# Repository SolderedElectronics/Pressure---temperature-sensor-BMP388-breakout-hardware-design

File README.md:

# Pressure & temperature sensor  BMP388 breakout Hardware Design

## About the Product

|  |
| :----------------------------------------------------------: |
| [Buy Pressure & temperature sensor  BMP388 breakout](https://www.solde.red/333316) |

<INSERT PRODUCT DESCRIPTION>

---

## Repository Contents

This repository contains all design files for Pressure & temperature sensor  BMP388 breakout, organized as follows:

- **`CAD` folder**: Contains KiCAD design files, including:
  - Schematics
  - PCB layout
  - Panel PCB layout
  - Source 3D files in Fusion360, if any
  - All files are sorted by version with a detailed change log.
- **`OUTPUTS` folder**: Includes all production-ready files, such as:
  - Bill of Materials (BOM) and interactive BOM (iBOM)
  - PDF versions of schematics
  - 3D `.step` file of the board
  - 3D-printable models
  - Gerber files for PCB manufacturing
  - Image of the pinout of the board
  - Product image
  - Compliance, legal and generic sales documents

Refer to the `Change Log` in the CAD folder for details about updates between versions.

---

## Learn More About the Product

Beyond the repository, explore the following resources:

### Soldered Verify

The **Soldered Verify** system ensures every board you purchase from Soldered is fully functional. It also provides access to exclusive test data for your product. To get started, find the unique Soldered Verify ID on your product's packaging and enter the ID on the [Soldered Verify page](https://soldered.com/verify/) to access test results and additional product details.

### Soldered Community

Soldered Community is your go-to place for technical support. Our engineers track and answer all questions posted there, and it’s a great space for the maker community. Get answers to your questions and solutions for your challenges at [Soldered Community](https://soldered.com/community).

### solde.red

solde.red is an ultimate URL shortener and information hub. Access it by typing solde.red/ followed by your product SKU, e.g., [solde.red/333000](https://solde.red/333000), to find getting-started guides, datasheets, open-source hardware and software files, certifications, images, pinouts, and more. Read more about the shortener [here](https://solde.red/info/).

---

## Contributing

Contributions are welcome! Here’s how you can get involved:

- Submit pull requests to enhance the design or fix issues.
- Report bugs or problems by opening an issue.

We encourage community collaboration to make this product even better.

---

## About Soldered

[Soldered for Makers](https://soldered.com) specializes in designing and manufacturing electronic products tailored for enthusiasts, ranging from hobbyists to professionals. Our portfolio includes electronic boards, sensors, and actuators that are widely utilized in fields such as microelectronics, mechatronics, robotics, programming, and IoT. Every product we offer is designed in-house and built upon open-source hardware and software platforms. Proudly certified and manufactured within the European Union, our catalog likely includes the product you need for your project.

We complement these products with comprehensive tutorials and manuals, product descriptions, schematics, programming codes, and project examples. Our round-the-clock [customer and technical support](https://soldered.com/community) is available for all our products, irrespective of the sales channel. Soldered’s success and services reflect our maker community’s unwavering [trust](https://www.trustpilot.com/review/soldered.com), for which we are deeply grateful. Join our community and create using Soldered products.

---

## License

All Soldered open-source hardware (OSH) is under The TAPR Open Hardware License. Read more in the LICENSE file located in this repository.

**Disclaimer:**

No warranty - all designs in this repository are distributed in the hope that they will be useful, but without any warranty. They are provided "AS IS", therefore without warranty of any kind, either expressed or implied. The entire quality and performance of what you do with the contents of this repository are your responsibility. In no event Soldered Electronics will be liable for your damages, or losses, including any general, special, incidental, or consequential damage arising out of the use or inability to use the contents of this repository. 

---

## Have fun!

Thank you for your support from your fellow makers at Soldered Electronics.

Happy Making!

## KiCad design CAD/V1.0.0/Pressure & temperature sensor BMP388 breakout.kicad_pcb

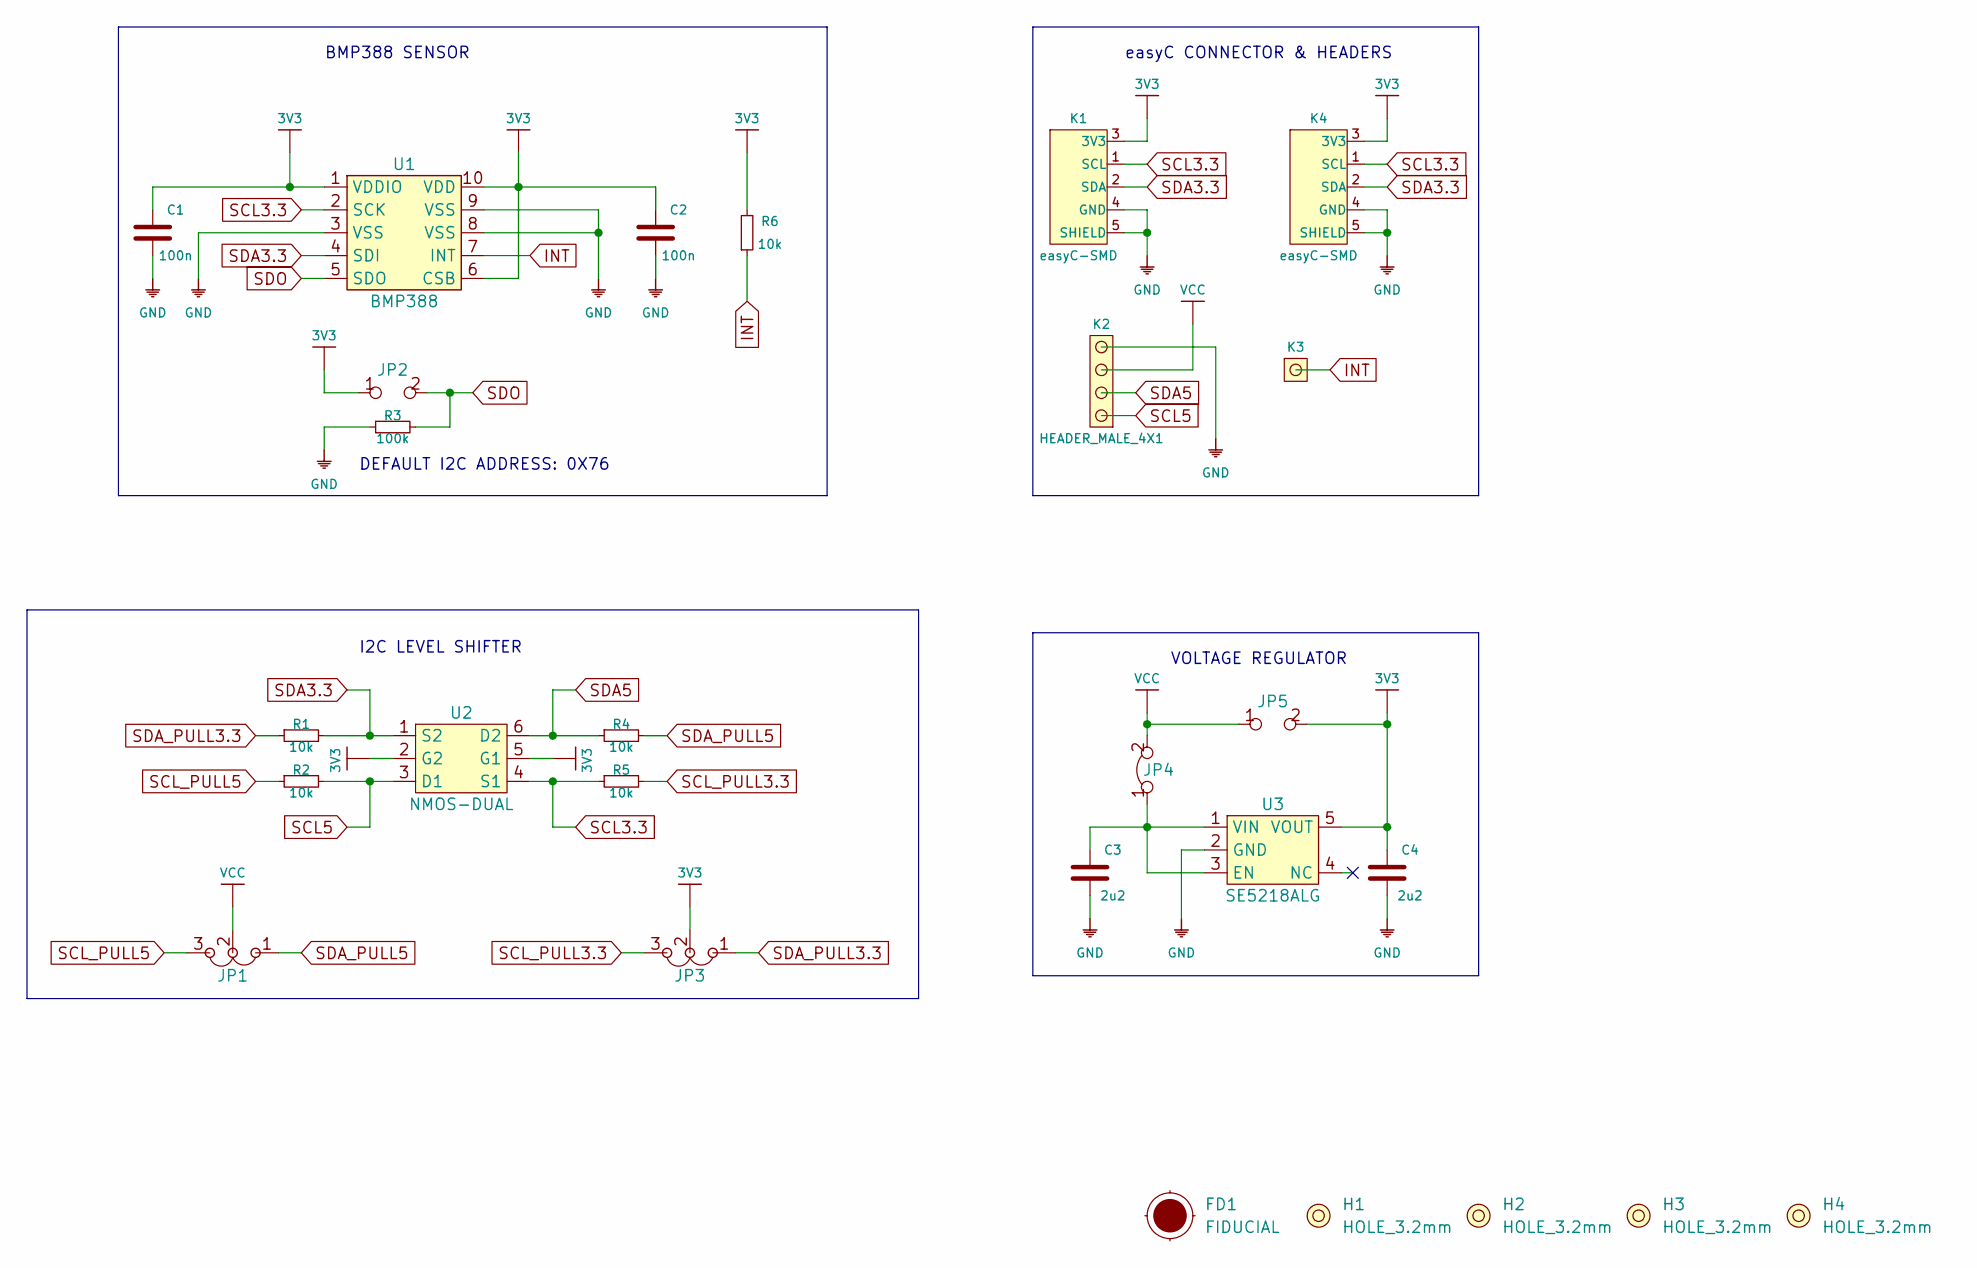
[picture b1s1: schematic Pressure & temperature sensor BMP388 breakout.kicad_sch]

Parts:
C1, C2: 100n; 0603C
C3, C4: 2u2; 0603C
FD1: FIDUCIAL; FIDUCIAL_23
H1, H2, H3, H4: HOLE_3.2mm
JP1, JP3: SMD_JUMPER_3_PAD_TRACE
JP2, JP5: SMD_JUMPER
JP4: SMD-JUMPER-CONNECTED_TRACE_SOLDERMASK
K1, K4: easyC-SMD; easyC-connector
K2: HEADER_MALE_4X1
K3: HEADER_MALE_1X1
R1, R2, R4, R5, R6: 10k; 0603R
R3: 100k; 0603R
U1: BMP388
U2: NMOS-DUAL; SOT-363
U3: SE5218ALG; SOT-23-5

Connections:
3V3: C1.2, C2.2, C4.2, JP2.1, JP3.2, JP5.2, K1.3 (3V3), K4.3 (3V3), R6.2, U1.1 (VDDIO), U1.6 (CSB), U1.10 (VDD), U2.2 (G2), U2.5 (G1), U3.5 (VOUT)
GND: C1.1, C2.1, C3.1, C4.1, K1.4 (GND), K1.5 (SHIELD), K2.4, K4.4 (GND), K4.5 (SHIELD), R3.1, U1.3 (VSS), U1.8 (VSS), U1.9 (VSS), U3.2 (GND)
INT: K3.1, R6.1, U1.7 (INT)
unnamed: C3.2, JP4.1, U3.1 (VIN), U3.3 (EN)
SCL3.3: K1.1 (SCL), K4.1 (SCL), R5.1, U1.2 (SCK), U2.4 (S1)
SCL5: K2.1, R2.2, U2.3 (D1)
SCL_PULL3.3: JP3.3, R5.2
SCL_PULL5: JP1.3, R2.1
SDA3.3: K1.2 (SDA), K4.2 (SDA), R1.2, U1.4 (SDI), U2.1 (S2)
SDA5: K2.2, R4.1, U2.6 (D2)
SDA_PULL3.3: JP3.1, R1.1
SDA_PULL5: JP1.1, R4.2
SDO: JP2.2, R3.2, U1.5 (SDO)
VCC: JP1.2, JP4.2, JP5.1, K2.3

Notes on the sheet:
BMP388 SENSOR
VOLTAGE REGULATOR
I2C LEVEL SHIFTER
easyC CONNECTOR & HEADERS
DEFAULT I2C ADDRESS: 0X76

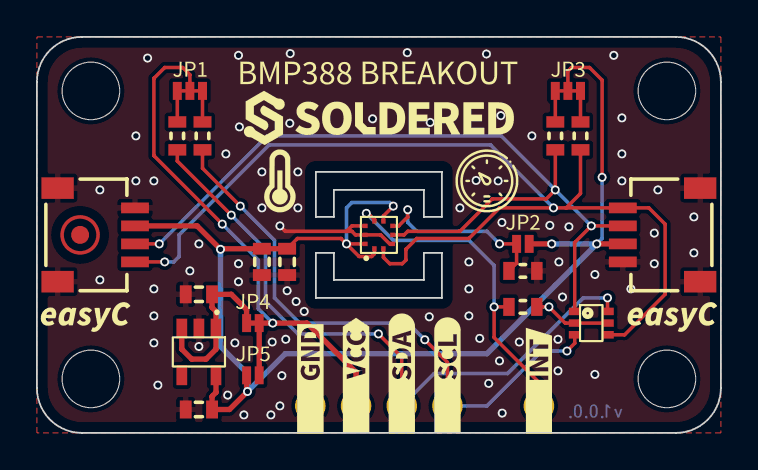
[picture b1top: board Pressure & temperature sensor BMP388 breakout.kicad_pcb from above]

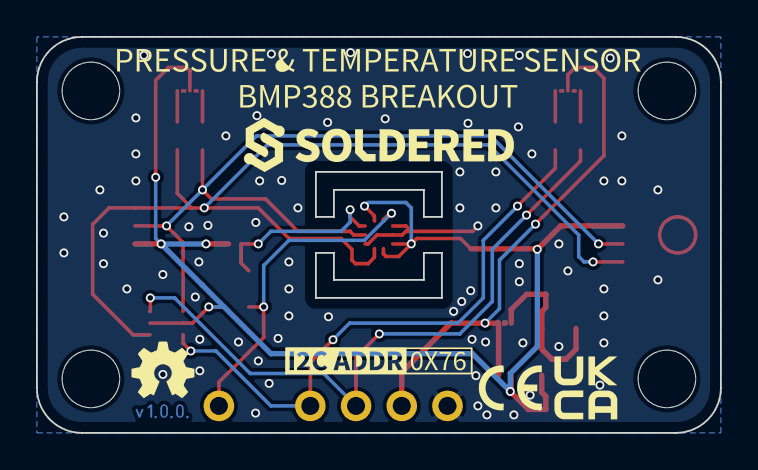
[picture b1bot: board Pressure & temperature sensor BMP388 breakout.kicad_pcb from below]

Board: 2 copper layers, 38.0 x 22.0 mm, 42 parts (4 on the bottom side), 14 nets.

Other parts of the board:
Ref**: Val**; Version1.0.0.
kibuzzard-6540E3E9: G***; kibuzzard-6540E3E9
kibuzzard-6540E3FA: G***; kibuzzard-6540E3FA
kibuzzard-6540E22C: G***; kibuzzard-6540E22C
kibuzzard-6540E41D: G***; kibuzzard-6540E41D
kibuzzard-6540E239: G***; kibuzzard-6540E239
kibuzzard-6540E248: G***; kibuzzard-6540E248
kibuzzard-6540E253: G***; kibuzzard-6540E253
kibuzzard-6540E409: G***; kibuzzard-6540E409
kibuzzard-6540E413: G***; kibuzzard-6540E413
kibuzzard-6540E637: G***; kibuzzard-6540E637
kibuzzard-6540EFF4, kibuzzard-6540EFF4#2: G***; kibuzzard-6540EFF4
kibuzzard-654100A7: G***; kibuzzard-654100A7
kibuzzard-65410794: G***; kibuzzard-65410794

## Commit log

2024-10-20 Updating open source files.
